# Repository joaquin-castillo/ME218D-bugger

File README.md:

# ME218D-bugger
Design files and documentation for the ME 218 D-bugger. The D-bugger is a tool for ME 218 student students to monitor and visualize the Events and Services Framework.

## PCBA fabrication and assembly
### Fab House
We had [JLCPCB](https://jlcpcb.com/) fabricate the boards and assemble the bottom sides. We elected to solder the top sides ourselves because, in addition to the three thru-hole components, there are only four 1206 SMD components on the top sides, and having both sides assembled with have cost significantly more. 1206 SMD packages are not difficult to solder by hand with the right equipment. If you are new to SMD soldering, see this [Intro to Soldering](https://sites.google.com/stanford.edu/soldering-internal/learning?authuser=0) tutorial page to learn the basics and best practices of hand soldering. A lesson we learned was to avoid no-clean solder flux and opt for water-soluble solder flux instead. This can be cleaned with isopropyl alcohol (at least 90%) or water and will not leave the board sticky and goopy after soldering.

The fabrication files needed to place an order with JLC are listed below:
- *Intermediary_revC_fab_20221219.zip*
- *Intermediary_revC_jlc_bottom.csv*
- *Intermediary_revC_4layer-bottom-pos.csv*

If for any reason you need to regenerate the fab files, JLC has some tutorials on [How to generate Gerber and Drill files](https://support.jlcpcb.com/article/194-how-to-generate-gerber-and-drill-files-in-kicad-6) and [How to generate the BOM and Centroid file](https://support.jlcpcb.com/article/84-how-to-generate-the-bom-and-centroid-file-from-kicad) specifically for KiCAD. The BOM and centroid file (aka pick and place file) are used for component assembly. In our experience, getting the centroid file in the right position and orientation relative to the board preview in JLC's quoting tool was a little finicky. This doesn't have to be perfect as JLC will have an engineer look at your files and correct anything before you approve the order. Something else to note is that for assembly, JLC requires some non-plated tooling hole to be added to the board for their processes. These have already been added to the design, but in case you want to see their requirements, that can be found on this page: [How to add tooling holes for PCB assembly order](https://support.jlcpcb.com/article/92-how-to-add-tooling-holes-for-smt-assembly-order).

### In House
Upon receiving the board from the fab house, they will still require a few components to be hand soldered. This includes:
- DIP-28 Socket (for the PIC)
- 3-pin header
- USB C receptacle
- 1206 SMD Green LED
- 1206 SMD Blue LEDs x2
- 1206 SMD 620 Ohm resistor

These can be found in the *Intermediary_revC_BOM.xlsx* file with links for DigiKey. The image below shows all seven components to be hand soldered:

Additionally, the boards must be configured at assembly to work with either the CP2102N serial bridge, or the PIC32's native USB. To do this, simply create solder bridges on the three jumper pads on the back side of the board as shown below:

To reconfigure the boards in the future, simply wick away the solder bridges and resolder the opposite pads.

## Enclosure

## Firmware
### PIC32 Microcontroller
The PIC needs to be programmed with the latest version of the D-bugger firmware. The latest firmware can be found [here]. Using a breadboard or ZIF socket, program the PIC with the SNAP programmer through MPLAB.

### CP2102N Serial Bridge
Though the serial bridge will work out-of-the-box, it should be configured to enable the RX and TX toggle LEDs, which are disabled by default. These LEDs are helpful for troublshooting communications issues from the target or to the host.

To do this, you must download Silicon Labs [Simplicity Studio](https://www.silabs.com/developers/simplicity-studio) and install it on your computer. You may be asked to create an account. Once installed, plug the D-bugger into your computer before opening the application. Once open, you shoud see the following window. If not, close or cancel out of any pop-up windows that may have appeared.

The CP2102N serial bridge should appear under **Connected Devices**. Click on **Start** to continue to the next screen.

Next, click on **Create New Project**.

The example project selected should be the **Xpress Configuration Project**. Click on **Next** to continue.

Here you can rename the project and choose where it will be saved. Once you're done, click on **Finish**.

You are now able to configure the chip's firmware. To enable the RX and TX toggle LEDs, scroll down to **Port Configuration: GPIO**. Be careful not to scroll with your cusor over a dropdown menu as the menu can cycle through its options and set some undesired configuration.

Under **Alternate Function**, for **GPIO0** and **GPIO1** select **TX Toggle** and **RX Toggle** from their respective dropdown menus. No other reconfigurations are necessary for the D-bugger. Click on **Save** and **Program To Device** to reprogram the chip.

In the pop-up window, ensure the CP2102N chip is selected and click on **OK**.

To confirm that the device has been successfully programed, you will see the following message in the **Status** window. You are now done and may now close out of the application!

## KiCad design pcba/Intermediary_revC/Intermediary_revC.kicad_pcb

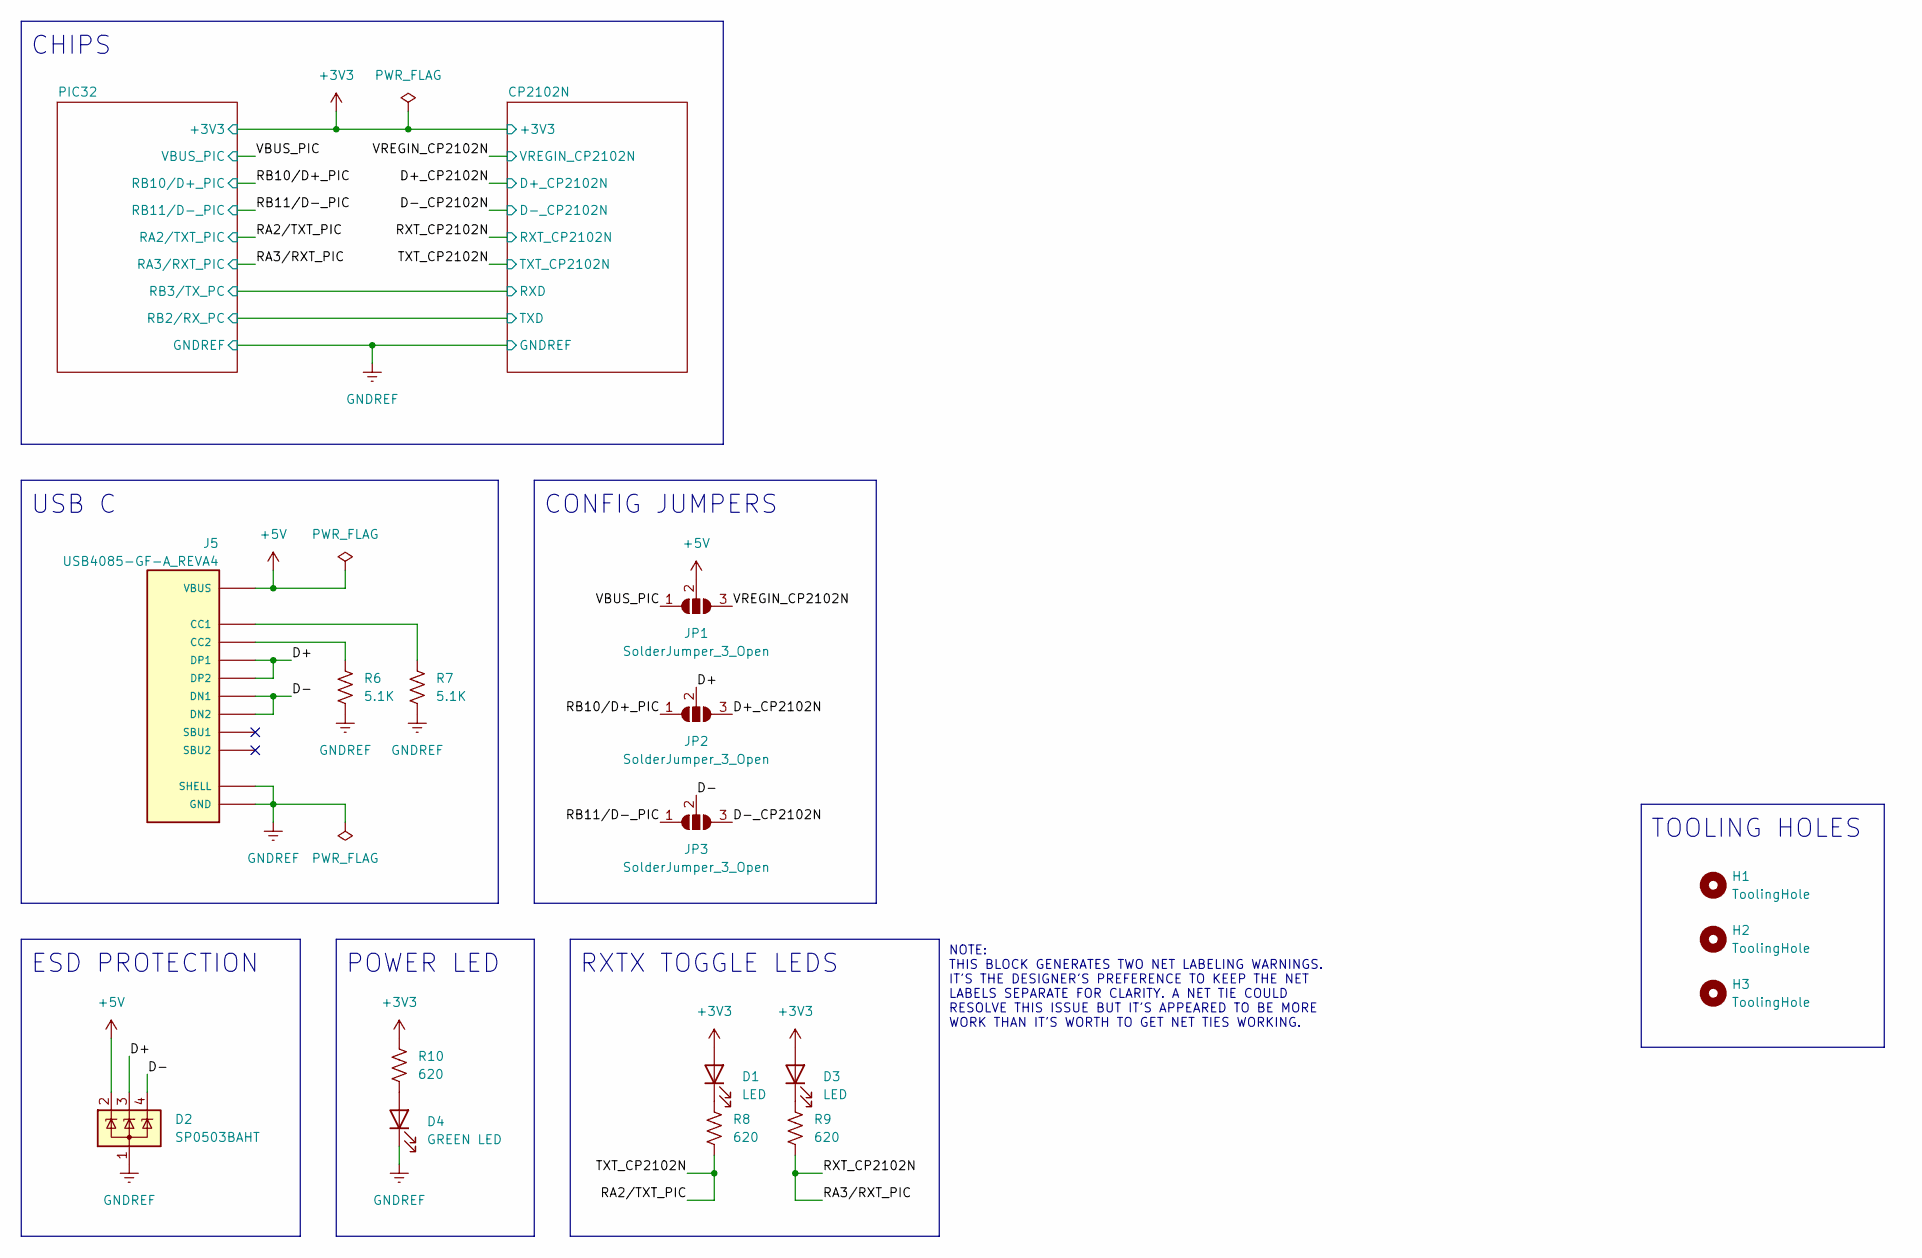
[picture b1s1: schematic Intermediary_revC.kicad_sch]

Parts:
D1, D3: LED; LED_1206_3216Metric
D2: SP0503BAHT; SOT-143
D4: GREEN LED; LED_1206_3216Metric
H1, H2, H3: ToolingHole; JLCPCB_Tooling_Hole
J5: USB4085-GF-A_REVA4; GCT_USB4085-GF-A_REVA4; PARTREV A4
JP1, JP2, JP3: SolderJumper_3_Open; SolderJumper-3_P2.0mm_Open_TrianglePad1.0x1.5mm_NumberLabels
R6, R7: 5.1K; R_1206_3216Metric
R8, R9, R10: 620; R_1206_3216Metric

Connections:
+3V3: D1.2 (A), D3.2 (A), R10.1; also elsewhere on the board
+5V: D2.2 (K), J5.A4 (VBUS), J5.A9 (VBUS), J5.B4 (VBUS), J5.B9 (VBUS), JP1.2 (C)
/D+: D2.3 (K), J5.A6 (DP1), J5.B6 (DP2), JP2.2 (C)
/D+_CP2102N: JP2.3 (B); also elsewhere on the board
/D-: D2.4 (K), J5.A7 (DN1), J5.B7 (DN2), JP3.2 (C)
/D-_CP2102N: JP3.3 (B); also elsewhere on the board
/RA2/TXT_PIC: R8.2; also elsewhere on the board
/RA3/RXT_PIC: R9.2; also elsewhere on the board
/RB10/D+_PIC: JP2.1 (A); also elsewhere on the board
/RB11/D-_PIC: JP3.1 (A); also elsewhere on the board
/VBUS_PIC: JP1.1 (A); also elsewhere on the board
/VREGIN_CP2102N: JP1.3 (B); also elsewhere on the board
GNDREF: D2.1 (A), D4.1 (K), J5.A1 (GND), J5.A12 (GND), J5.B1 (GND), J5.B12 (GND), J5.S1 (SHELL), J5.S2 (SHELL), J5.S3 (SHELL), J5.S4 (SHELL), R6.2, R7.2; also elsewhere on the board
unnamed: D1.1 (K), R8.1
unnamed: D3.1 (K), R9.1
unnamed: D4.2 (A), R10.2
unnamed: J5.A5 (CC1), R7.1
unnamed: J5.B5 (CC2), R6.1

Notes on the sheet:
ESD PROTECTION
USB C
CONFIG JUMPERS
POWER LED
NOTE: THIS BLOCK GENERATES TWO NET LABELING WARNINGS. IT'S THE DESIGNER'S PREFERENCE TO KEEP THE NET LABELS SEPARATE FOR CLARITY. A NET TIE COULD RESOLVE THIS ISSUE BUT IT'S APPEARED TO BE MORE WORK THAN IT'S WORTH TO GET NET TIES WORKING.
CHIPS
TOOLING HOLES
RXTX TOGGLE LEDS

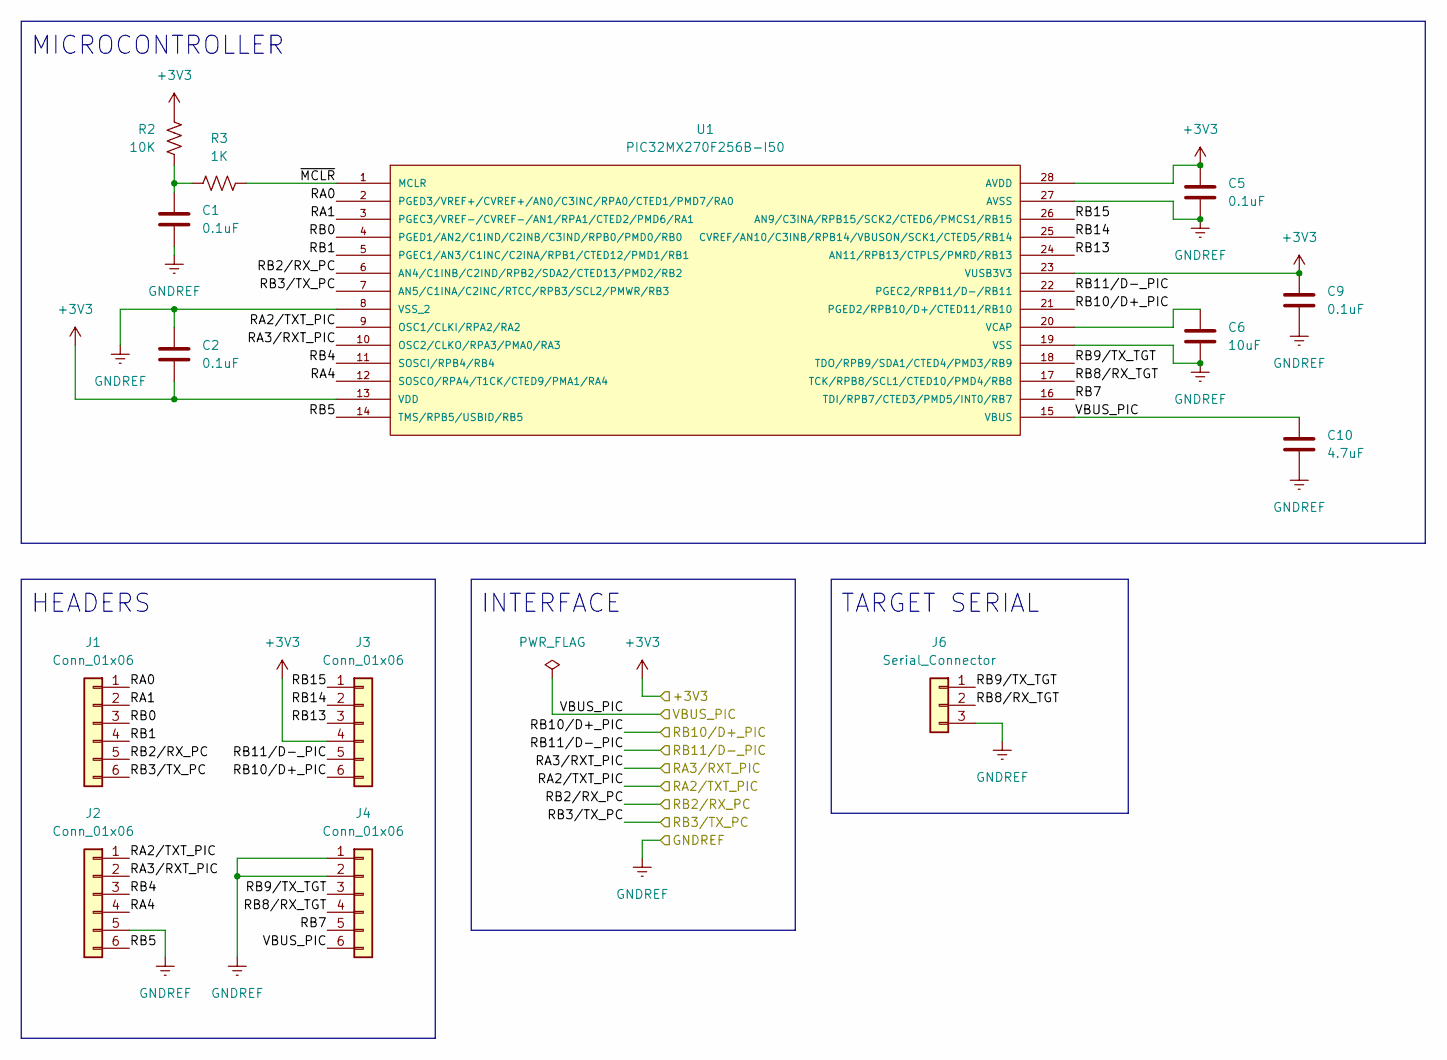
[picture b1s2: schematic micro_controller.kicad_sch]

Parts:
C1, C2, C5, C9: 0.1uF; C_1206_3216Metric
C6: 10uF; C_1206_3216Metric
C10: 4.7uF; C_1206_3216Metric
J1, J2, J3, J4: Conn_01x06; PinSocket_1x06_P2.54mm_Vertical
J6: Serial_Connector; PinSocket_1x03_P2.54mm_Horizontal
R2: 10K; R_1206_3216Metric
R3: 1K; R_1206_3216Metric
U1: PIC32MX270F256B-I50; OST_ED281DT

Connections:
+3V3: C2.2, C5.1, C9.1, J3.4, R2.1, U1.13 (VDD), U1.23 (VUSB3V3), U1.28 (AVDD); also elsewhere on the board
/CP2102N/RXD: J1.6, U1.7 (AN5/C1INA/C2INC/RTCC/RPB3/SCL2/PMWR/RB3); also elsewhere on the board
/CP2102N/TXD: J1.5, U1.6 (AN4/C1INB/C2IND/RPB2/SDA2/CTED13/PMD2/R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); also elsewhere on the board
/PIC32/RA0: J1.1, U1.2 (PGED3/VREF+/CVREF+/AN0/C3INC/RPA0/CTED1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)
/PIC32/RA1: J1.2, U1.3 (PGEC3/VREF-/CVREF-/AN1/RPA1/CTED2/PMD6/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)
/PIC32/RA4: J2.4, U1.12 (SOSCO/RPA4/T1CK/CTED9/PMA1/RA4)
/PIC32/RB0: J1.3, U1.4 (PGED1/AN2/C1IND/C2INB/C3IND/RPB0/PMD0/R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)
/PIC32/RB1: J1.4, U1.5 (PGEC1/AN3/C1INC/C2INA/RPB1/CTED12/PMD1/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)
/PIC32/RB4: J2.3, U1.11 (SOSCI/RPB4/RB4)
/PIC32/RB5: J2.6, U1.14 (TMS/RPB5/USBID/RB5)
/PIC32/RB7: J4.5, U1.16 (TDI/RPB7/CTED3/PMD5/INT0/RB7)
/PIC32/RB8/RX_TGT: J4.4, J6.2, U1.17 (TCK/RPB8/SCL1/CTED10/PMD4/RB8)
/PIC32/RB9/TX_TGT: J4.3, J6.1, U1.18 (TDO/RPB9/SDA1/CTED4/PMD3/RB9)
/PIC32/RB13: J3.3, U1.24 (AN11/RPB13/CTPLS/PMRD/RB13)
/PIC32/RB14: J3.2, U1.25 (CVREF/AN10/C3INB/RPB14/VBUSON/SCK1/CTED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)
/PIC32/RB15: J3.1, U1.26 (AN9/C3INA/RPB15/SCK2/CTED6/PMCS1/RB15)
/PIC32/~MCLR: R3.2, U1.1 (MCLR)
/RA2/TXT_PIC: J2.1, U1.9 (OSC1/CLKI/RPA2/RA2); also elsewhere on the board
/RA3/RXT_PIC: J2.2, U1.10 (OSC2/CLKO/RPA3/PMA0/RA3); also elsewhere on the board
/RB10/D+_PIC: J3.6, U1.21 (PGED2/RPB10/D+/CTED11/RB10); also elsewhere on the board
/RB11/D-_PIC: J3.5, U1.22 (PGEC2/RPB11/D-/RB11); also elsewhere on the board
/VBUS_PIC: C10.1, J4.6, U1.15 (VBUS); also elsewhere on the board
GNDREF: C1.2, C2.1, C5.2, C6.2, C9.2, C10.2, J2.5, J4.1, J4.2, J6.3, U1.8 (VSS_2), U1.19 (VSS), U1.27 (AVSS); also elsewhere on the board
unnamed: C1.1, R2.2, R3.1
unnamed: C6.1, U1.20 (VCAP)

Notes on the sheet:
INTERFACE
TARGET SERIAL
HEADERS
MICROCONTROLLER

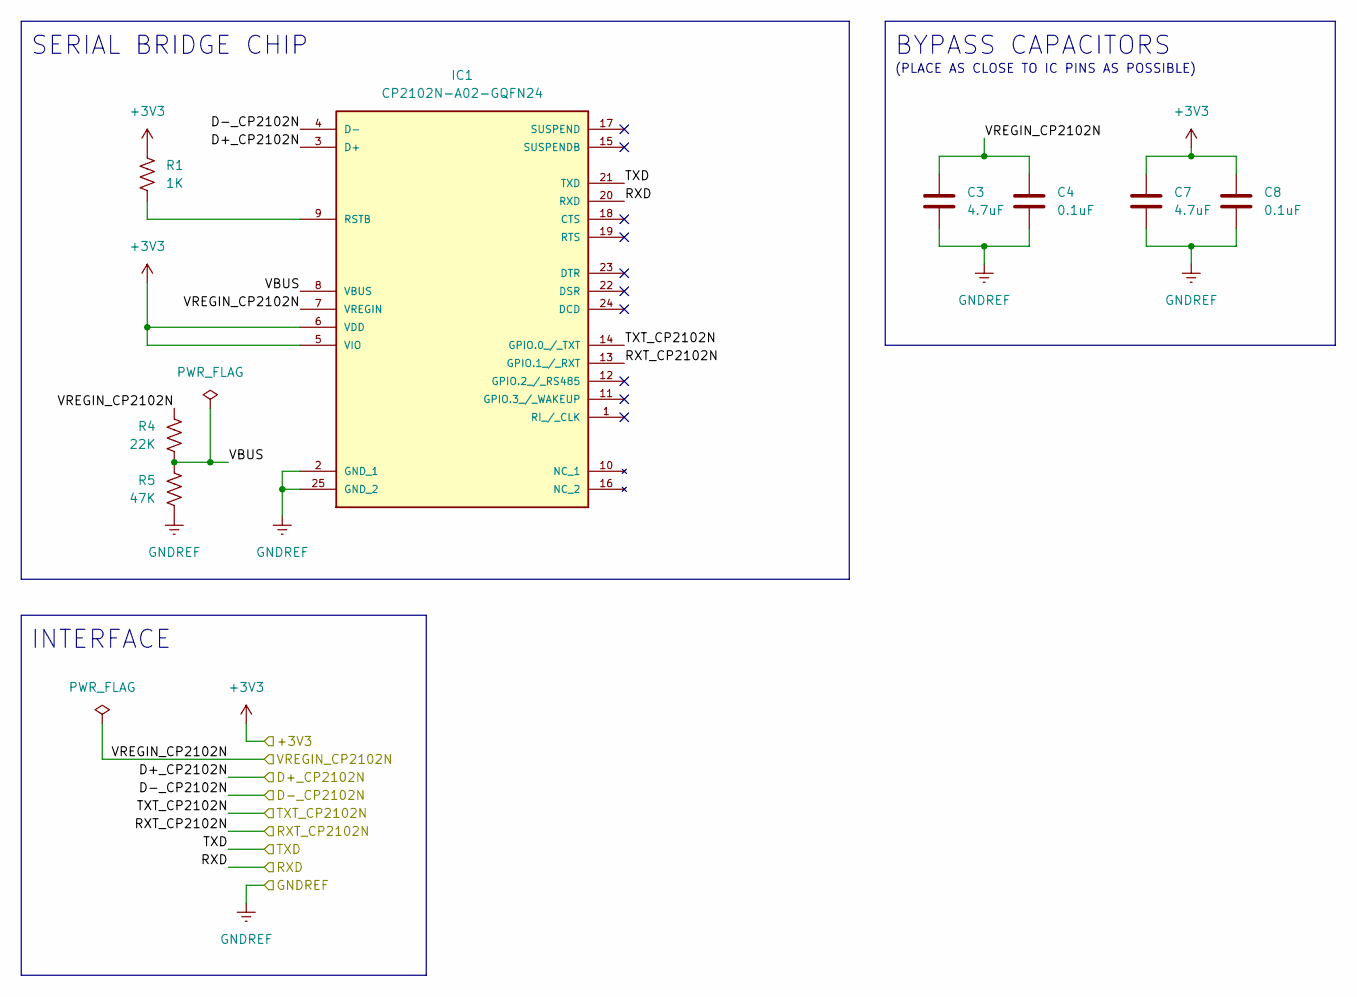
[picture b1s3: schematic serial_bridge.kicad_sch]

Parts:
C3, C7: 4.7uF; C_1206_3216Metric
C4, C8: 0.1uF; C_1206_3216Metric
IC1: CP2102N-A02-GQFN24; QFN50P400X400X80-25N; MOUSER_PART_NUMBER 634-CP2102NA02GQFN24
R1: 1K; R_1206_3216Metric
R4: 22K; R_1206_3216Metric
R5: 47K; R_1206_3216Metric

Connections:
+3V3: C7.1, C8.1, IC1.5 (VIO), IC1.6 (VDD), R1.1; also elsewhere on the board
/CP2102N/RXD: IC1.20 (RXD); also elsewhere on the board
/CP2102N/TXD: IC1.21 (TXD); also elsewhere on the board
/CP2102N/VBUS: IC1.8 (VBUS), R4.2, R5.1
/D+_CP2102N: IC1.3 (D+); also elsewhere on the board
/D-_CP2102N: IC1.4 (D-); also elsewhere on the board
/RA2/TXT_PIC: IC1.14 (GPIO.0_/_TXT); also elsewhere on the board
/RA3/RXT_PIC: IC1.13 (GPIO.1_/_RXT); also elsewhere on the board
/VREGIN_CP2102N: C3.1, C4.1, IC1.7 (VREGIN), R4.1; also elsewhere on the board
GNDREF: C3.2, C4.2, C7.2, C8.2, IC1.2 (GND_1), IC1.25 (GND_2), R5.2; also elsewhere on the board
unnamed: IC1.9 (RSTB), R1.2

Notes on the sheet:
INTERFACE
BYPASS CAPACITORS
SERIAL BRIDGE CHIP
(PLACE AS CLOSE TO IC PINS AS POSSIBLE)

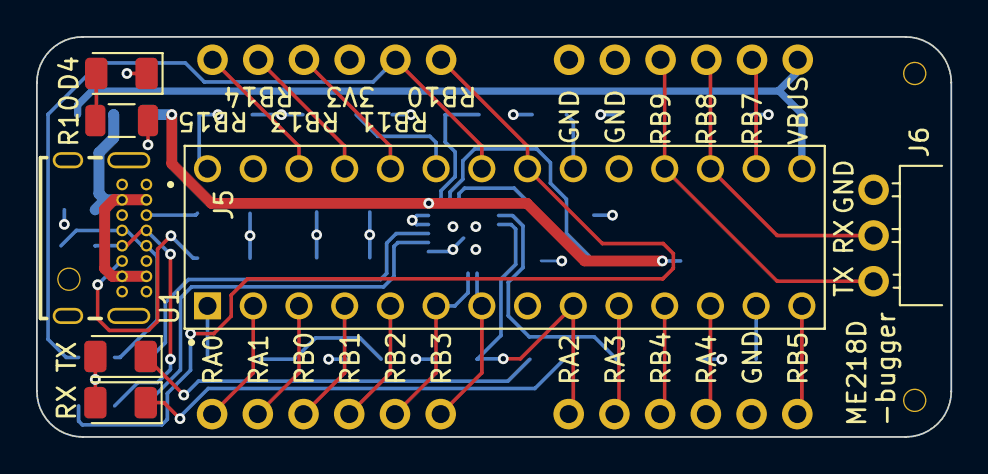
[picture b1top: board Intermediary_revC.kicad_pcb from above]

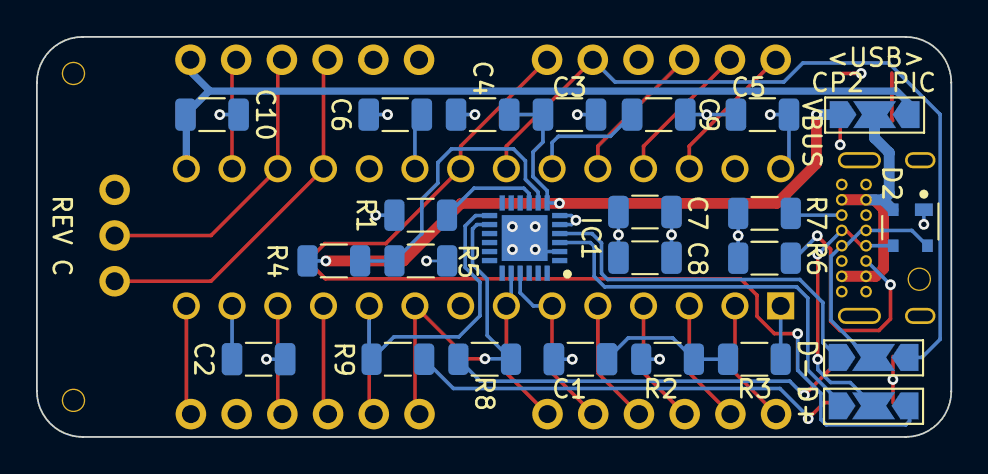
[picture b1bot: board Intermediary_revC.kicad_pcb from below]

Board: 4 copper layers, 50.8 x 22.2 mm, 38 parts (27 on the bottom side), 38 nets.

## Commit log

2023-01-13 Add git ignore with recommended KiCAD settings
2023-01-13 Add design and fab files for intermediary revC and enclosure
2023-01-13 Write fab and assembly section of readme and modify gitignore to allow csv
2023-01-20 Add first part of Firmware section
2023-01-22 Add soldering images
2023-01-22 Add soldering images to readme
2023-01-29 Write instructions for flashing serial bridge chip
2023-01-29 Add Simplicity Studio screenshots
2023-01-29 Finish firmware section
